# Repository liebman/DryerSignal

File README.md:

# Simple Dryer Signal
I have a cheap dryer, it has no "done" signal.  I'm adding one using a current sensor and an ATTiny85

[DryerSignal](DryerSignal) contains the code for the ATTiny85.  I used [Eclipse with an Arduino plugin](http://sloeber.io) for development.  If you want to use the Arduino IDE then create an empty file named DryerSignal.ino

[eagle](eagle) contains the [Eagle](https://www.autodesk.com/products/eagle/overview) design files.

Its a work in progress....

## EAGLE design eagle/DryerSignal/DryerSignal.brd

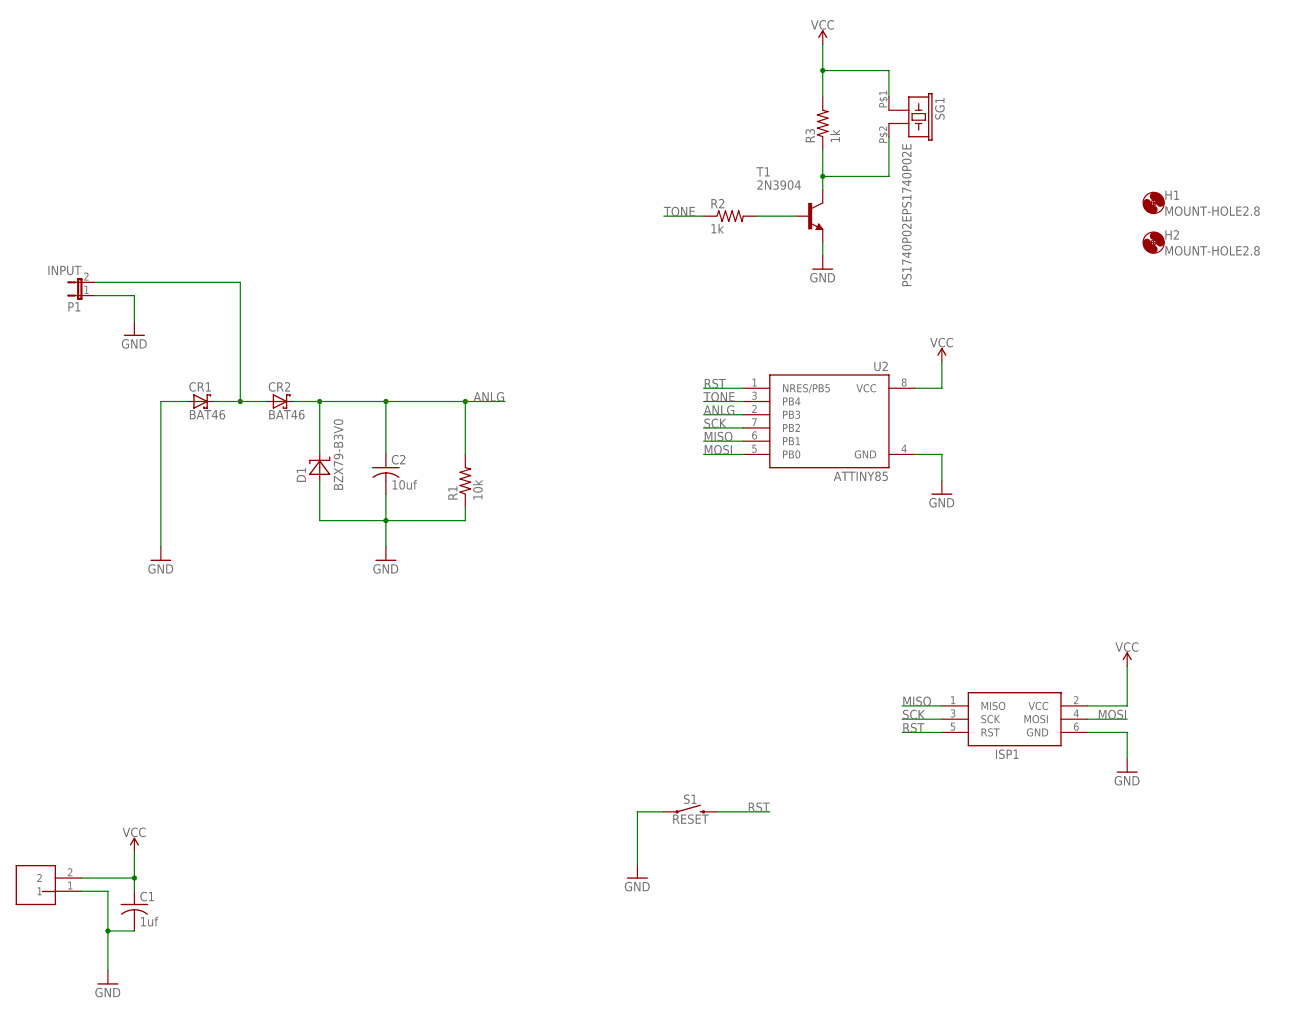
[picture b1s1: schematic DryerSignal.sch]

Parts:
C1: 1uf; C050-025X075
C2: 10uf; C050-025X075
CR1, CR2: BAT46; DO35-10
D1: BZX79-B3V0; DO35-10
H1, H2: MOUNT-HOLE2.8; 2,8
ISP1: AVRISP-BOX
J1: 4.5v; 2_PIN_JST-XH
P1: INPUT; 1X02
R1: 10k; 0207/10
R2, R3: 1k; 0207/10
S1: RESET; 1X02
SG1: PS1740P02EPS1740P02E; PS1740P02E
T1: 2N3904; TO92
U2: ATTINY85; PDIP08_300MIL

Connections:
ANLG: C2.1, CR2.C, D1.C, R1.2, U2.2 (PB3)
GND: C1.2, C2.2, CR1.A, D1.A, ISP1.6 (GND), J1.1, P1.1, R1.1, S1.1, T1.3 (E), U2.4 (GND)
INPUT: CR1.C, CR2.A, P1.2
MISO: ISP1.1 (MISO), U2.6 (PB1)
MOSI: ISP1.4 (MOSI), U2.5 (PB0)
unnamed: R2.2, T1.2 (B)
unnamed: R3.1, SG1.P$2 (2), T1.1 (C)
RST: ISP1.5 (RST), S1.2, U2.1 (NRES/PB5)
SCK: ISP1.3 (SCK), U2.7 (PB2)
TONE: R2.1, U2.3 (PB4)
VCC: C1.1, ISP1.2 (VCC), J1.2, R3.2, SG1.P$1 (1), U2.8 (VCC)

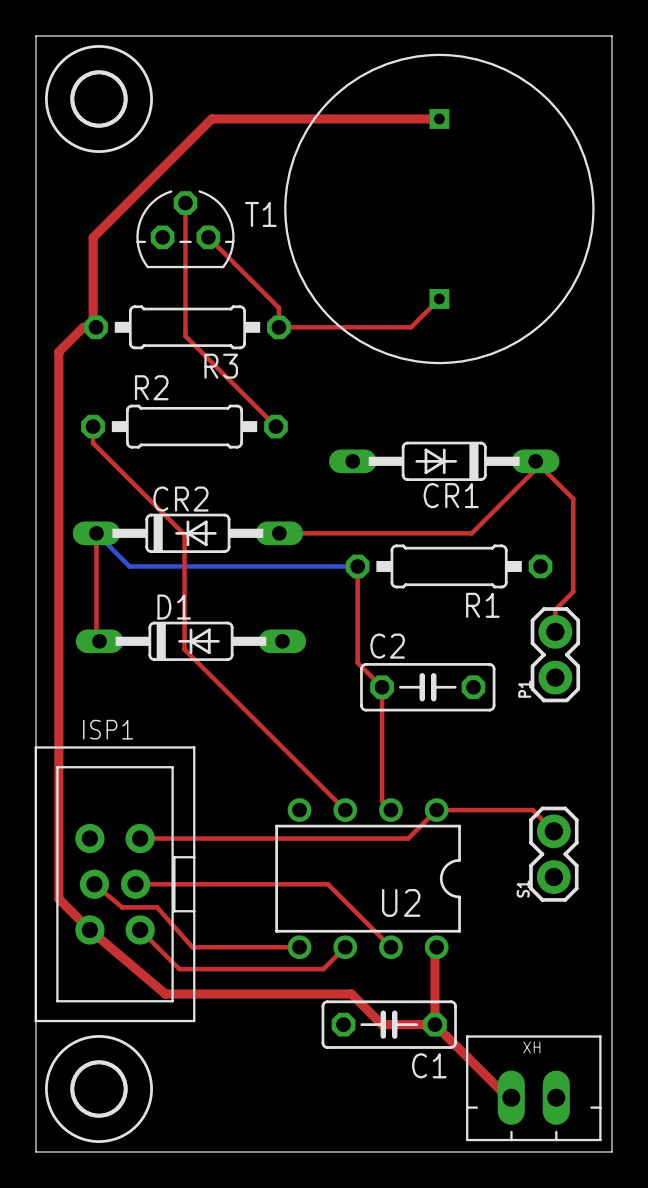
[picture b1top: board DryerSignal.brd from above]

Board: 2 copper layers, 32.0 x 62.0 mm, 17 parts (0 on the bottom side), 11 nets.

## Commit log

2017-10-11 initial import, still WIP
2017-10-12 updated schematic & board to remove voltage regulator

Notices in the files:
parts and their libraries:
SparkFun-PowerSymbols: Licensing: Creative Commons ShareAlike 4.0 International - https://creativecommons.org/licenses/by-sa/4.0
